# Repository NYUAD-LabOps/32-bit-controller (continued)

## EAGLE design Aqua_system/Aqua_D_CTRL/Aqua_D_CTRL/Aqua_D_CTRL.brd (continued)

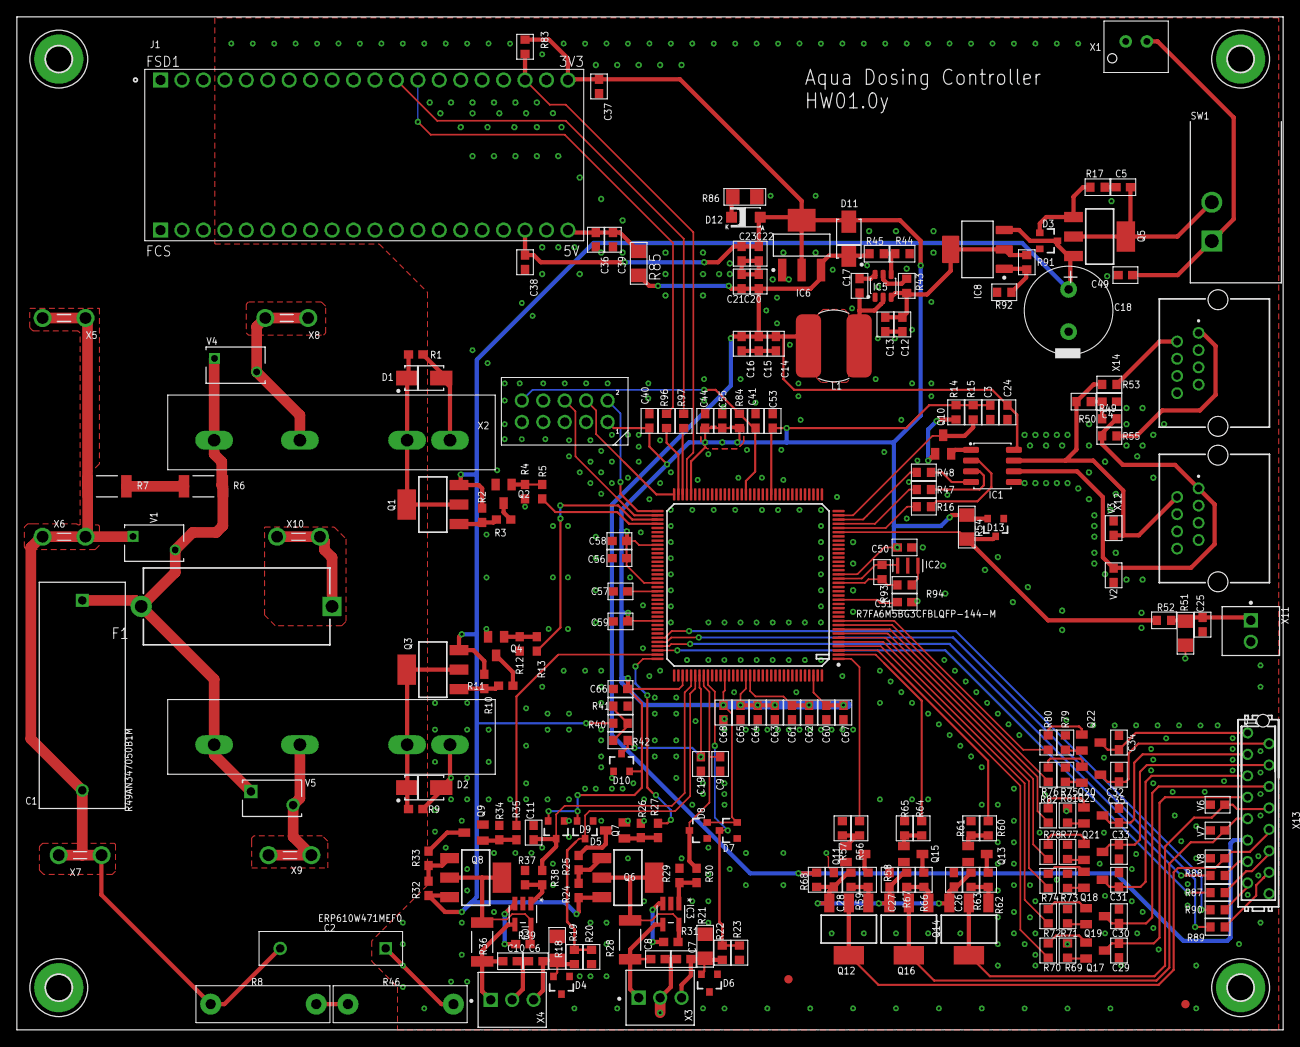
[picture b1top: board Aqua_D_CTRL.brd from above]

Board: 2 copper layers, 150.0 x 120.0 mm, 234 parts (0 on the bottom side), 138 nets.

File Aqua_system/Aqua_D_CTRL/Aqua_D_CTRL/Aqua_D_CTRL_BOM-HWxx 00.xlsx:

Qty | MFN | Value | Device | Package | Parts | DESCRIPTION.1 | LIB_STATUS | MFR | OUR_STOCK | PART_VALUE | PRICE-1 | SUPPLIER-1
5 | 0603ESDA-24N | 0603ESDA-24N | 0603ESDA-24N | 0603 | V2, V3, V6, V7, V8 | Varistor 0603 SMD Bidirectional 50V 24V |  | BORN |  |  | 0.01 | LCSC
4 | Open Source | 0R 1% | R_0603 | R0603 | R53, R55, R68, R94
1 | R_Open_1206 | 0R 1% | R_1206 | R1206 | R85 |  | Verified
2 | Open Source | 100K 1% | R_0603 | R0603 | R20, R23
1 | R_Open_1206 | 100K 1% | R_1206 | R1206 | R51 |  | Verified
8 |  | 100R 1% | R_0603 | 0603 | R5, R13, R27, R30, R31, R35, R38, R39
20 | Open Source | 100R 1% | R_0603 | R0603 | R42, R49, R50, R52, R56, R60, R64, R70, R72, R74, R76, R78, R80, R82, R87, R88,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
2 | R_Open_1206 | 100R 1% | R_1206 | R1206 | R18, R21 |  | Verified
8 | Open Source | 100nF/ 100V | C_0603 | 0603 | C5, C12, C13, C17, C19, C21, C23, C49
4 | Open Source | 100nF/100V | C_0603 | 0603 | C8, C9, C10, C11 |  |  |  |  | 100nF/100V
8 | Open Source | 100nF/100V | C_0603 | 0603 | C3, C4, C6, C7, C24, C25, C38, C39
24 | Open Source | 100nF/50V | C_0603 | 0603 | C26, C27, C28, C29, C30, C31, C32, C33, C34, C35, C41, C50, C51, C53, C55, C56,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
14 |  | 10K 1% | R_0603 | 0603 | R1, R2, R3, R4, R9, R10, R11, R12, R24, R25, R26, R32, R33, R34
13 | Open Source | 10K 1% | R_0603 | R0603 | R14, R17, R57, R58, R59, R61, R62, R63, R65, R66, R67, R84, R93
7 | Open Source | 10uF/25V | C_0603 | 0603 | C14, C15, C16, C20, C22, C62, C64
4 | Open Source | 1K 1% | R_0603 | R0603 | R15, R19, R22, R83
1 | R_Open_1206 | 1K 1% | R_1206 | R1206 | R54 |  | Verified
1 | Open Source | 1k 1% | R_0603 | R0603 | R91
5 | Open Source | 1uF/25V | C_0603 | 0603 | C36, C37, C40, C44, C65
1 | Open Source | 1unF/50V | C_0603 | 0603 | C67
2 |  | 2.2K 1% | R_0603 | 0603 | R29, R37
1 | Open Source | 2.8K 1% | R_0603 | R0603 | R41
2 |  | 220K 1% | R_2010 | R2010 | R6, R7 |  |  |  |  |  | 0.11 | Digikey
3 | Open Source | 22K 1% | R_0603 | R0603 | R40, R43, R45
1 | Open Source | 24K 1% | R_0603 | R0603 | R92
1 | 26-21/GPC-F3138B/CA | 26-21/GPC-F3138B/CA | 26-21/GPC-F3138B/CA | SMD1206-LED | D12 | Green SMD LED 1206, 160mcd | Prototype | Everlight | 50 | Green LED | 0.06 | LCSC
1 | 282834-2 | 282834-2 | 282834-2 | TE_282834-2_0 | X11 | Connector Header Terminal Block 2 Positions, 1 Row, 2.54mm, THT |  | TE |  |  | 0.8 | Digikey
2 | 282834-3 | 282834-3 | 282834-3 | TE_282834-3_0 | X3, X4 | Connector 3 Position THT 1 Row 2.54mm pitch side entry wire to board |  | TE |  |  | 1.7 | Digikey
7 | 2N7002 | 2N7002 | 2N7002 | SOT23 | Q2, Q4, Q7, Q9, Q11, Q13, Q15 | NMOSFET, 500mA, 60V, Vth 2.5V | Prototype | Diodes, Guangdong Hotetech,NXP | 100 | NMOSFET | 0.02 | LCSC
1 | Open Source | 3K01 1% | R_0603 | R0603 | R44
10 | Open Source | 470R 1% | R_0603 | R0603 | R16, R47, R48, R69, R71, R73, R75, R77, R79, R81
1 | 50PX470MEFC10X20 | 50PX470MEFC10X20 | 50PX470MEFC10X20 | CAPACITOR-ELKO-RM5-10X16 | C18 | 470uF Â±20% 50V 10mm 20mm 5mm 2000Hrs @ 105â„ƒ -55â„ƒ ~ +105â„ƒ | Prototype | Rubicon | 20 | 470uF/50V | 0.14 | LCSC
1 | 696101000002 | 696101000002 | 696101000002 | FUSE_RM22.6 | F1 | Fuse Block 10 A 250V 1 Circuit Cartridge Through Hole | Prototype | Wurth Elektronik | 10 | 10A 5mmx20mm | 0.64 | Digikey
6 |  | 726386-2TE_726386-2 | 726386-2TE_726386-2 | TE_726386-2 | X5, X6, X7, X8, X9, X10 | Terminals, Faston, GDS-Flachstecker 6.3x0.8mm, TE
1 | R_Open_1206 | 82R 1% | R_1206 | R1206 | R86 |  | Verified
1 | B2B-XH-AM(LF)(SN) | B2B-XH-AM(LF)(SN) | B2B-XH-AM(LF)(SN) | B2B-XH-AM(LF)(SN) | X1 | Connector, 2 pins, Header THT , Pitch 2.5mm, JST, Vertical |  | JST |  |  | 0.03 | LCSC
1 |  | B72205S0271K1011 | B72205S0271K1011 | EPCOS_B72205S0271K101_MODIFIED | V5 | VARISTOR 205V 800A DISC 5MM
2 | B72205S0271K1011 | B72205S0271K101B72205S2131K101 | B72205S0271K101B72205S2131K101 | EPCOS_B72205S0271K101_0 | V1, V4 | VARISTOR 205V 800A DISC 5MM | Verified | EPCOS | 10 | 430V, 400A | 0.31 | Digikey
6 | BAS40-04,215 | BAS40-04,215 | BAS40-04,215 | SOT23-3 | D5, D7, D8, D9, D10, D13 | Schottky dual series, SOT23, 40V, 120mA |  | NXP |  | BAS40-04 | 0.19 | Mouser
8 | BC817 | BC817 | BC817 | SOT23 | Q10, Q17, Q18, Q19, Q20, Q21, Q22, Q23 | Transistor BJT NPN SOT23 45V 0.5A |  | NXP |  |  | 0.03 | Mouser
1 | CSTNE8M00G520000R0 | CSTNE8M00G520000R0 | CSTNE8M00G520000R0 | CSTNE8M00G520000R0 | IC2 | 8MHz Â±0.5% 10pF 40Î© SMD3213-3P Ceramic Resonators | Prototype | Murata |  | 8MHz, 0.5% | 0.12 | LCSC
8 | DMP6185SEQ-13 | DMP6185SEQ-13 | DMP6185SEQ-13 | SOT223 | Q1, Q3, Q5, Q6, Q8, Q12, Q14, Q16 | PMOSFET, SOT-223, 60V, 3A |  | Diodes | 100 | DMP6185SEQ-13 | 0.18 | LCSC
1 | ERP610W471MEF0 | ERP610W471MEF0 | ERP610W471MEF0 | CAP-P12.5-H15-W4-D1 | C2 | 470 pF Â±20% 760VAC Ceramic Capacitor Y5U (E) Radial X1,Y1 | Prototype | Kemet | 150 | 470pF/760VAC | 0.42 | Digikey
1 |  | ESP32-PICO-KIT | ESP32-PICO-KIT | XCVR_ESP32-PICO-KIT | J1 | ESP32-PICO-D4 series Transceiver |  |  |  | None | None
2 |  | FIDUCIAL | FIDUCIAL | FIDUCIAL | FID1, FID2
2 | KB20C06A | KB20C06A | KB20C06A | RELAY_KYOTO_KF0604D | K1, K2 | Solid State Relay, Out AC 280VAC, In DC 32V |  | Kyotto
1 | L101011MS02Q | L101011MS02Q | L101011MS02Q | L101011MS02Q | SW1 | Slide Switch, SPST, 4A, 28VDC | Prototype | C&K |  | SW 4A/28V | 1.66 | Mouser
1 | LD1117S33TR | LD1117S33TR | LD1117S33TR | SOT223_LD1117S33TR | IC6 | LDO,Fixed 15V 3.3V 1.3V @ 800mA SOT-223 | Verified | STmicro, Diodes, TI, | 10 | xx1117x33xx | 0.07 | LCSC
1 |  | LM317AEMP | LM317AEMP | SOT223_LM317AEMP | IC8 | Linear Voltage Regulator IC Positive Adjustable Output 1.5A SOT-223-4
2 | LT6106CS5#TRPBF | LT6106CS5#TRPBF | LT6106CS5#TRPBF | SOT-23-5 | IC3, IC4 | Current Sense Amplfier 36V, SOT23-5 |  | Analog Devices |  | LT6106CS5 | 1.5 | Mouser
1 |  | MICROMATCH-16 | MICROMATCH-16 | MICROMATCH-16 | X13 | MicroMaTch 16 8-215464-6 / 1-215464-6
1 | MMBZ4696-HE3-18 | MMBZ4696-HE3-18 | MMBZ4696-HE3-18 | SOT23-3 | D3 | Zener Diodes 9.1 Volt 0.225W 5% AUTO |  | Vishay | 500 | 9V 5% | 0.06 | Mouser
4 |  | MOUNT-PAD-ROUND3.0 | MOUNT-PAD-ROUND3.0 | 3,0-PAD | H1, H2, H3, H4 | MOUNTING PAD, round
2 | PESD36VS2UT | PESD36VS2UT | PESD36VS2UT | SOT23-3 | D4, D6 | ESD Diode Voff=36V, Vclamp=60V, SOT23 |  | NXP | 150 |  | 0.15 | Mouser
1 | R49AN347050B1M | R49AN347050B1M | R49AN347050B1M | R49AN347050B1M | C1 | Film,X1,470nF/330Vac,THT | Verified | Kemet | 8 | 470nF/330VAC | 1.51 | Digikey
1 | R7FA6M5BG3CFB | R7FA6M5BG3CFBLQFP_144_20X20_REN-M | R7FA6M5BG3CFBLQFP_144_20X20_REN-M | LQFP_144_20X20_REN-M | U2 | LQFP-144 ARM33 MCU with micro ROS Support |  | Renesas
2 |  | RJ45-8L-B | RJ45-8L-B | RJ45-NO-SHIELD | X12, X14
2 | RNF12FTD10M0 | RNF12FTD10M0 | RNF12FTD10M0 | RES-RM12.5-VR37 | R8, R46 | 10 MOhms Â±1% 0.5W, 1/2W Through Hole Resistor Axial Flame Retardant Coating, S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 | Prototype | Stackpole Electronics Inc |  | 10Meg 5% | 0.29 | Digikey
2 | RL73K2HR68JTE | R_2010 | R_2010 | R2010 | R28, R36 |  |  |  |  | 680mR | 0.11 | Digikey
1 | SN65HVD3082EDR | SN65HVD3082EDR | SN65HVD3082EDR | SOIC8 | IC1 | RS485 Transciever, 200Kbps, SOIC-8 , ALT: TP8485E-SR (3Peak) | Prototype | TI,3Peak | 10 | RS485 Driver | 0.30 | LCSC
1 | SRN8040TA-220M | SRN8040TA-220M | SRN8040TA-220M | SRN8040TA-220M | L1 | FIXED IND 22UH 2.9A SMD, 73m-Ohm, Bourns | Verified | Bourns | 10 | 22uH/2.9A |  | Digikey
3 | SS14-LTP | SS14 | SS14 | SMA | D1, D2, D11 | Diode Schottky 1A/40V (SMA) | Prototype | MCC | 10 | Schottky 1A/40V | 0.05 | LCSC
1 | TPS54202DDCR | TPS54202DDCR | TPS54202DDCR | SOT23-6 | IC5 | 2A 28V SOT-23-6 Sync Buck | Prototype | Texas Instruments | 40 | TPS54202 | 1.8 | LCSC
1 | WF2549-2WS05S0B01 | WF2549-2WS05S0B01 | WF2549-2WS05S0B01 | X10_100MIL_2XROW_VERT | X2 | X10, 10 Pins, Header, Pitch 2.54 wire to board 2xrows, THT |  | WCON |  |  | 0.25 | LCSC

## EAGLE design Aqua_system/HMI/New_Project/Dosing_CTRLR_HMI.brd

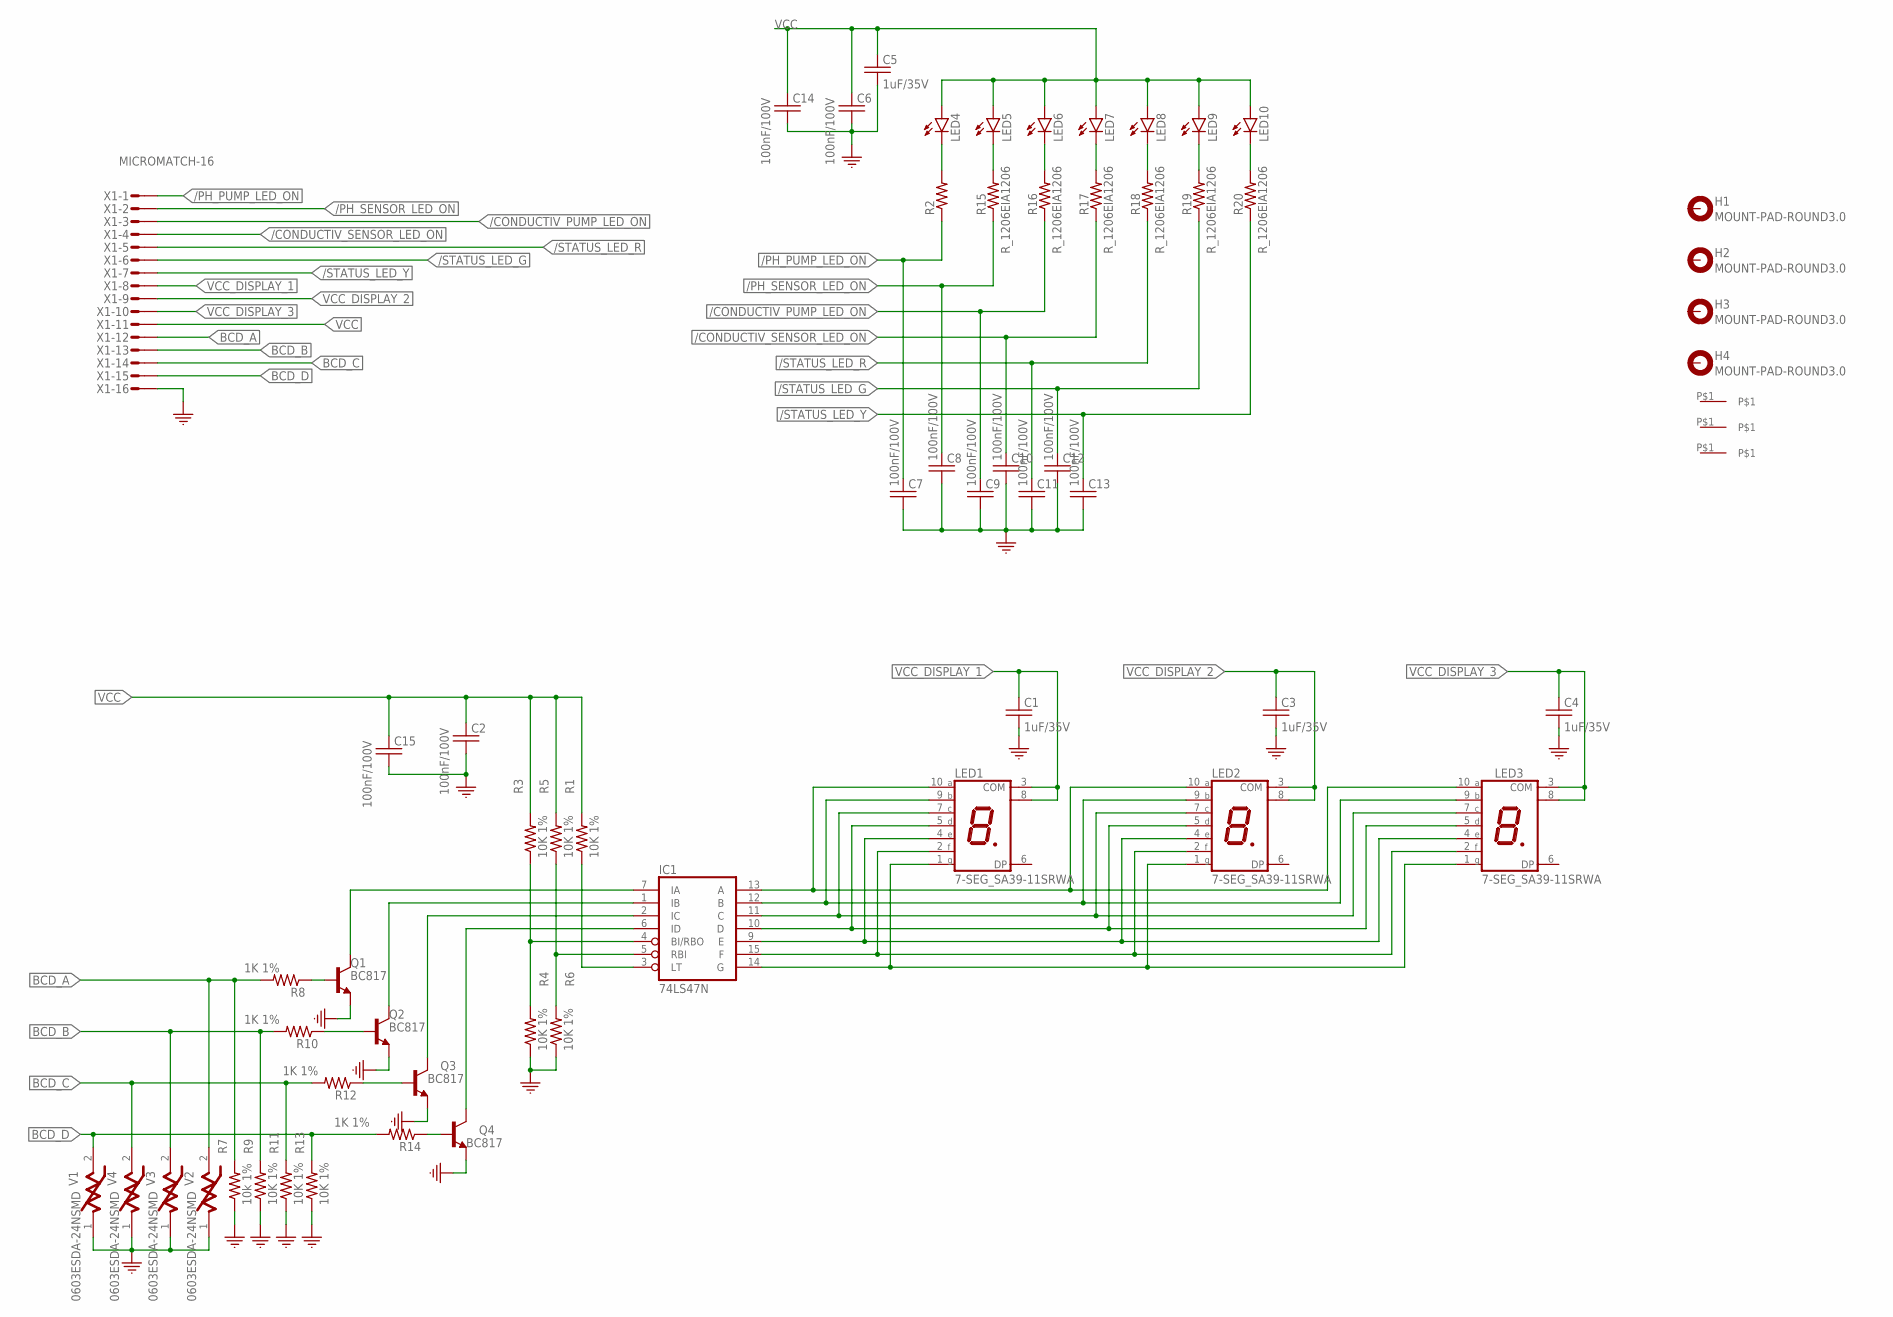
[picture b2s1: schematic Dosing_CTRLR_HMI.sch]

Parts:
C1, C3, C4, C5: 1uF/35V; EIA0603
C2, C6, C7, C8, C9, C10, C11, C12, C13, C14, C15: 100nF/100V; EIA0603
FID1, FID2, FID3: FIDUCIAL
H1, H2, H3, H4: MOUNT-PAD-ROUND3.0; 3,0-PAD
IC1: 74LS47N; DIL16
LED1, LED2, LED3: 7-SEG_SA39-11SRWA; SA39-11SRWA
LED4, LED5, LED6, LED7, LED8, LED9, LED10: LED5MM
Q1, Q2, Q3, Q4: BC817; SOT23
R1, R3, R4, R5, R6, R9, R11, R13: 10K 1%; EIA0603
R2, R15, R16, R17, R18, R19, R20: R_1206EIA1206; EIA1206
R7: 10k 1%; EIA0603
R8, R10, R12, R14: 1K 1%; EIA0603
V1, V2, V3, V4: 0603ESDA-24NSMD; EIA0603
X1: MICROMATCH-16

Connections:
/CONDUCTIV_PUMP_LED_ON: C9.1, R16.1, X1.3
/CONDUCTIV_SENSOR_LED_ON: C10.1, R17.1, X1.4
/PH_PUMP_LED_ON: C7.1, R2.1, X1.1
/PH_SENSOR_LED_ON: C8.1, R15.1, X1.2
/STATUS_LED_G: C12.1, R19.1, X1.6
/STATUS_LED_R: C11.1, R18.1, X1.5
/STATUS_LED_Y: C13.1, R20.1, X1.7
BCD_A: R7.2, R8.2, V2.2, X1.12
BCD_B: R9.2, R10.2, V3.2, X1.13
BCD_C: R11.2, R12.2, V4.2, X1.14
BCD_D: R13.2, R14.2, V1.2, X1.15
GND: C1.2, C2.2, C3.2, C4.2, C5.2, C6.2, C7.2, C8.2, C9.2, C10.2, C11.2, C12.2, C13.2, C14.2, C15.2, IC1.8 (GND), Q1.2 (E), Q2.2 (E), Q3.2 (E), Q4.2 (E), R4.1, R6.1, R7.1, R9.1, R11.1, R13.1, V1.1, V2.1, V3.1, V4.1, X1.16
unnamed: IC1.13 (A), LED1.10 (A), LED2.10 (A), LED3.10 (A)
unnamed: IC1.12 (B), LED1.9 (B), LED2.9 (B), LED3.9 (B)
unnamed: IC1.11 (C), LED1.7 (C), LED2.7 (C), LED3.7 (C)
unnamed: IC1.10 (D), LED1.5 (D), LED2.5 (D), LED3.5 (D)
unnamed: IC1.9 (E), LED1.4 (E), LED2.4 (E), LED3.4 (E)
unnamed: IC1.15 (F), LED1.2 (F), LED2.2 (F), LED3.2 (F)
unnamed: IC1.14 (G), LED1.1 (G), LED2.1 (G), LED3.1 (G)
unnamed: IC1.4 (BI/RBO), R3.1, R4.2
unnamed: IC1.3 (LT), R1.1
unnamed: Q4.1 (B), R14.1
unnamed: IC1.5 (RBI), R5.1, R6.2
unnamed: Q3.1 (B), R12.1
unnamed: LED4.K (C), R2.2
unnamed: Q2.1 (B), R10.1
unnamed: LED5.K (C), R15.2
unnamed: LED6.K (C), R16.2
unnamed: Q1.1 (B), R8.1
unnamed: IC1.7 (IA), Q1.3 (C)
unnamed: IC1.1 (IB), Q2.3 (C)
unnamed: IC1.2 (IC), Q3.3 (C)
unnamed: IC1.6 (ID), Q4.3 (C)
unnamed: LED7.K (C), R17.2
unnamed: LED8.K (C), R18.2
unnamed: LED9.K (C), R19.2
unnamed: LED10.K (C), R20.2
VCC: C2.1, C5.1, C6.1, C14.1, C15.1, IC1.16 (VCC), LED4.A, LED5.A, LED6.A, LED7.A, LED8.A, LED9.A, LED10.A, R1.2, R3.2, R5.2, X1.11
VCC_DISPLAY_1: C1.1, LED1.3 (COM), LED1.8 (COM), X1.8
VCC_DISPLAY_2: C3.1, LED2.3 (COM), LED2.8 (COM), X1.9
VCC_DISPLAY_3: C4.1, LED3.3 (COM), LED3.8 (COM), X1.10

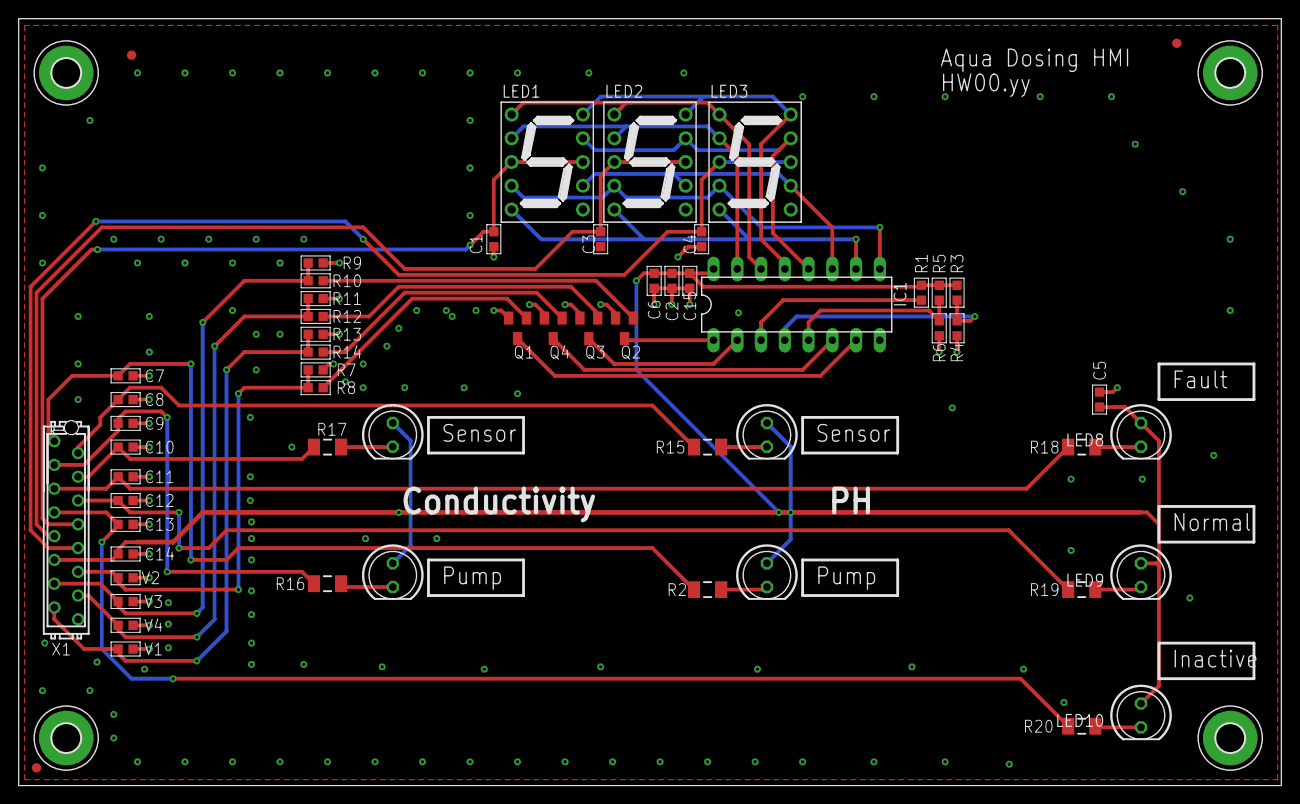
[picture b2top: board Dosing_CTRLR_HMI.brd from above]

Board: 2 copper layers, 135.0 x 82.0 mm, 62 parts (0 on the bottom side), 41 nets.

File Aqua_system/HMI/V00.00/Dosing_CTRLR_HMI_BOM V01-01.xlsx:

Qty | Value | Device | Package | Parts | Description | DESCRIPTION | MF | MFN | MFR | MPN | OC_FARNELL | OC_NEWARK | PART_VALUE | POPULARITY | PRICE-1 | SUPPLIER-1
7 |  | LED5MM | LED5MM | LED4, LED5, LED6, LED7, LED8, LED9, LED10 | LED |  |  |  |  |  |  |  |  | 93
4 | 0603ESDA-24NSMD | 0603ESDA-24NSMD | EIA0603 | V1, V2, V3, V4 |  | aristor 0603 SMD Bidirectional 50V 24V |  | 0603ESDA-24N | Bourns |  |  |  |  |  |  | LCSC
11 | 100nF/100V | C_0603EIA0603 | EIA0603 | C2, C6, C7, C8, C9, C10, C11, C12, C13, C14, C15
8 | 10K 1% | R_0603 | EIA0603 | R1, R3, R4, R5, R6, R9, R11, R13 |  |  |  | Open Source 0603
1 | 10k 1% | R_0603 | EIA0603 | R7 |  |  |  | Open Source 0603
4 | 1K 1% | R_0603 | EIA0603 | R8, R10, R12, R14 |  |  |  | Open Source 0603
4 | 1uF/35V | C_0603EIA0603 | EIA0603 | C1, C3, C4, C5
3 | 7-SEG_SA39-11SRWA | 7-SEG_SA39-11SRWA | SA39-11SRWA | LED1, LED2, LED3 | Kingbright 14.2mm (0.56 INCH) SINGLE DIGIT NUMERIC DUISPLAY |  |  |  |  |  | unknown | unknown
1 | 74LS47N | 74LS47N | DIL16 | IC1 | BCD to seven segment DECODER/DRIVER |  |  |  |  |  |  |  |  | 0
4 | BC817 | BC817 | SOT23 | Q1, Q2, Q3, Q4 |  | Transistor BJT NPN SOT23 45V 0.5A |  | BC817 | NXP |  |  |  |  |  | 0.03 | Mouser
3 | FIDUCIAL | FIDUCIAL | FIDUCIAL | FID1, FID2, FID3
1 | MICROMATCH-16 | MICROMATCH-16 | MICROMATCH-16 | X1 | MicroMaTch 16 8-215464-6 / 1-215464-6 |  | FARNELL |  |  | 8-215464-6 | 3784680 | 26H3309
4 | MOUNT-PAD-ROUND3.0 | MOUNT-PAD-ROUND3.0 | 3,0-PAD | H1, H2, H3, H4 | MOUNTING PAD, round |  |  |  |  |  |  |  |  | 17
7 | R_1206EIA1206 | R_1206EIA1206 | EIA1206 | R2, R15, R16, R17, R18, R19, R20 |  |  |  | Open Source R1206
